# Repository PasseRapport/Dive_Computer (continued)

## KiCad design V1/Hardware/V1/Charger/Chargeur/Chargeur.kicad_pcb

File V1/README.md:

# Freediving Computer

A freediving computer prototype I built to test two main ideas: **tap navigation via accelerometer** and **wireless charging** in a completely sealed case.

As a maker, building waterproof buttons and moving parts that survive water pressure without leaking is nearly impossible. To avoid leaks, I skipped physical buttons and external connectors entirely:
1. **Tap navigation** — tapping the case scrolls and selects menus; the accelerometer detects the shock direction.
2. **Wireless charging** — sealed inside the case with an LTC4120 receiver, powered by a custom induction dock.
3. **Magnetic power switch** — an external magnet disconnects the battery so it doesn't drain when stored.
4. **Custom 4-layer PCB** — designed around the form factor of an off-the-shelf color OLED module.

> **Status**: This V1 worked and proved the concept. I am now working on a **V2** that is more compact, with better integration and additional features.

---

## Demo

<p align="center"><em>Tap-based navigation through the interface — accelerometer detects directional impacts on the casing.</em></p>

<p align="center"><em>Live depth tracking during a test — automatic dive detection and surface recovery timer.</em></p>

---

## Key Features

| Category | Details |
|---|---|
| **Depth & Temperature** | Real-time tracking via MS5837-30BA (±2 mm resolution, 300–1200 hPa). Automatic fresh/salt water density compensation. |
| **Dive State Machine** | Auto-triggers at 1.0 m depth. Tracks dive time, max depth per dive, and session statistics. |
| **Surface Recovery Timer** | Starts automatically on surfacing. Color-coded: red until 2× dive time, then green. Auto-hides after 10 min. |
| **Session Statistics** | Max dive time, max depth, total dives, and device run time — all tracked per session. |
| **Tap Navigation** | LIS2DUX12 accelerometer detects directional taps on the casing. Left/right to scroll, down to select. No buttons, no dynamic seals. |
| **Magnetic Battery Cutoff** | Integrated magnetic switch isolates the LiPo battery with an external magnet (true 0 µA shelf storage while sealed). |
| **Wireless Charging** | Completely sealed enclosure — power delivered through the case via LTC4120 wireless power receiver. |
| **Display** | 1.27" SSD1351 color OLED (128×96), driven over SPI with DMA. LVGL handles 60 fps animated transitions. |
| **Battery Monitoring** | ADC with hardware calibration curve. Voltage divider maps LiPo range (3.0–4.2 V) to percentage. |
| **Deep Sleep** | Full power-off via menu. GPIO wakeup from accelerometer interrupt. OLED and SPI bus shut down cleanly. |

---

## Mechanical Design

The housing is a two-part sandwich assembly designed without push-buttons, external connectors, or dynamic seals. Waterproofing relies entirely on static seals: a perimeter O-ring evenly compressed between the two halves by 12 M2 screws, and a front protective glass bonded with UV-cure resin. The only physical control is an external magnetic slider that switches power through the solid case wall without any hull penetration.

<p align="center">
  <a href="https://cad.onshape.com/documents/cc2f090fad22f578b68190d0/w/ffbf50c58a8e366da5acdcdc/e/88baec5796e801b1a2b4a1f3">
    View the 3D model on Onshape ↗
  </a>
</p>

---

## Hardware Architecture

The electronics are split between the wrist unit and a dedicated charging dock.

### 1. Dive Computer Board (Wrist Unit)

The core electronics are built around a custom **4-layer PCB** designed in KiCad, dimensioned to mate directly with an off-the-shelf color OLED module:

- **Form Factor & Display**: Sourced a compact 1.27" 128×96 color OLED module (SSD1351 controller, SPI) and tailored the custom 4-layer PCB and enclosure footprint around this geometry.
- **MCU**: ESP32-C3 (RISC-V core, low power modes, BLE).
- **Pressure Sensor**: TE MS5837-30BA (gel-protected submersible pressure & temperature sensor on I2C).
- **Accelerometer**: ST LIS2DUX12 (ultra-low-power, configured for shock/tap detection with hardware interrupt).
- **Wireless Power Receiver**: Analog Devices LTC4120 with an internal Würth planar receiver coil (WE-WPCC-RX), delivering CC/CV charging to the internal 3.7V LiPo cell.
- **Magnetic Power Switch**: Integrated Hall-effect sensor / magnetic switch controlling a P-MOSFET gate, enabling complete physical battery disconnection via an external magnet without unsealing the housing.

| Component | Part | Role |
|---|---|---|
| MCU | ESP32-C3 | RISC-V core, sensor aggregation, LVGL rendering |
| Pressure Sensor | MS5837-30BA | Absolute pressure & temperature (I2C @ 100 kHz) |
| Accelerometer | LIS2DUX12 | Tap detection with hardware interrupt (I2C) |
| Wireless Charger RX | LTC4120 | Wireless power receiver & CC/CV LiPo charger |
| Magnetic Disconnect | A1102 + P-MOS | Physical battery isolation via external magnet (0 µA storage) |
| Display Module | SSD1351 (Off-the-shelf) | 1.27" 128×96 color OLED (SPI with DMA) |
| Battery | LiPo 3.7V | Single cell, monitored via calibrated ADC voltage divider |

### 2. Wireless Charger Dock (Transmitter)

A companion transmitter base powered via USB-C:

| Component | Part | Role |
|---|---|---|
| Transmitter IC | LTC4125 | 5W AutoResonant wireless power transmitter |
| Transmit Coil | Würth WE-WPCC-TX | 24 µH primary coil for inductive power transfer |
| Input | USB-C (5V) | Power supply |

Source files (KiCad projects, gerbers, BOM): [`Hardware/V1/`](Hardware/V1/)

---

## Software Architecture

The firmware is written in **C** on **ESP-IDF** with **FreeRTOS**. The codebase follows an MVC pattern:

```
Software/DiveComputer/main/
├── main.c                  # App entry, event loop, screen state machine
├── components/
│   ├── pressure_sensor.c   # MS5837 driver, depth calculation, calibration
│   ├── accelerometer.c     # LIS2DUX12 tap detection (ISR + burst analysis)
│   ├── battery.c           # ADC with hardware calibration curve
│   └── oled_display.c      # SSD1351 init, SPI+DMA, LVGL driver
└── ui/
    ├── ui_model.h          # Global state structure (dive_state_t)
    ├── ui_controller.c     # Dive logic, timers, brightness control
    ├── ui_layout.c         # All LVGL screens and refresh functions
    └── ui_layout.h         # Public UI API
```

### Task Model

| Task | Core | Priority | Rate | Role |
|---|---|---|---|---|
| `dive_sensor_task` | 1 | 5 | 4 Hz | Reads pressure sensor, computes depth, updates model |
| `lvgl_port_task` | 0 | 5 | 100 Hz | LVGL rendering and screen refresh |
| `tap_analyzer_task` | 0 | 10 | Event-driven | Wakes on accelerometer interrupt, analyzes shock direction |
| Main loop | 0 | 1 | 50 Hz | Polls tap events, drives screen state machine |

### Dive State Machine

```
                 depth > 1.0m
   ┌──────────┐ ───────────────> ┌──────────┐
   │ SURFACE  │                  │  DIVING  │ <──────┐
   └──────────┘                  └──────────┘        │
        ^                             │              │ depth > 1.0m
        │                             │ depth < 0.3m │ (next dive)
        │                             v              │
        │                      ┌─────────────┐       │
        └───────────────────── │  POST-DIVE  │ ──────┘
           recovery >= 10 min  │ (Recovery)  │
                               └─────────────┘

```

### Tap Detection Pipeline

The accelerometer's hardware tap interrupt wakes the ESP32, which performs a 100-sample burst read (~10 ms) to capture the full shock waveform. The axis with the largest amplitude delta wins, and its sign determines the direction. A 2000-unit noise floor filter rejects accidental vibrations.

```
[HW Interrupt] ──> [ISR Queue] ──> [Burst Read (100 samples)] ──> [Axis Analysis] ──> [Direction Filter] ──> [UI Event]
```

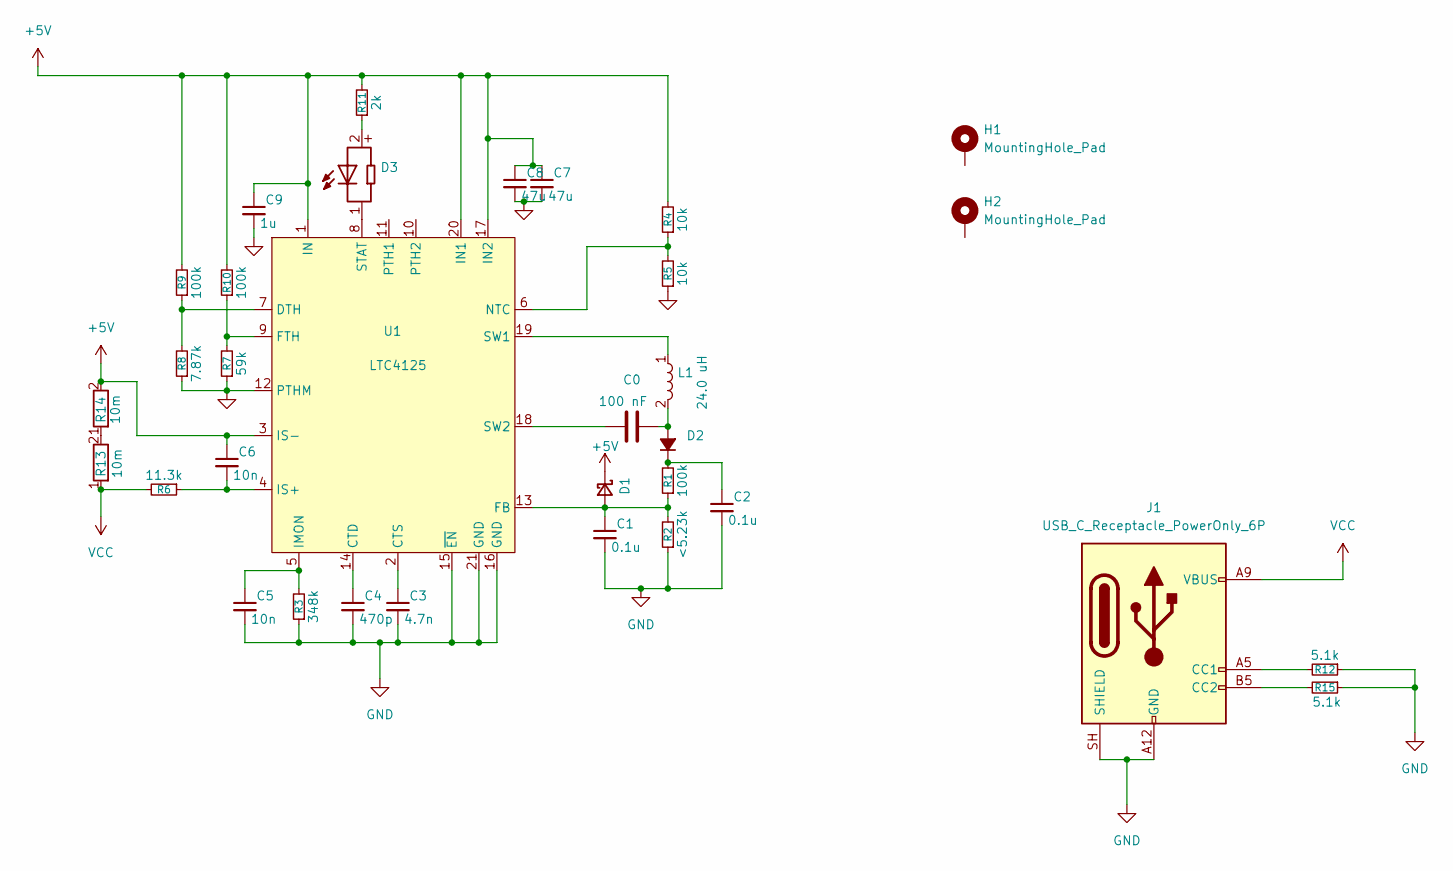
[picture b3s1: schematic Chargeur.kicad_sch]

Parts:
C0: 100 nF; C_Wurth_WCAP-FTBP-P7.5L10.5W5H11; Voltage 160; Part Number 890443322001CS
C1, C2: 0.1u; C_0603_1608Metric
C3: 4.7n; C_0603_1608Metric
C4: 470p; C_0603_1608Metric
C5, C6: 10n; C_0603_1608Metric
C7, C8: 47u; C_1206_3216Metric
C9: 1u; C_1206_3216Metric
D1: D_Schottky_Small; D_MicroSMP_LargeCathode
D2: D_Small_Filled; D_SOD-523
D3: 3535_150353BS74500; D_Wurth_WL-SMDC-3535; Part Number 150353BS74500
H1, H2: MountingHole_Pad; MountingHole_3.2mm_M3_DIN965_Pad
J1: USB_C_Receptacle_PowerOnly_6P; USB_C_Receptacle_GCT_USB4125-xx-x-0190_6P_TopMnt_Horizontal
L1: 24.0 uH; L_Wurth_WE-WPCC-TX_760308101107; Part Number 760308101107
R1, R9, R10: 100k; R_0603_1608Metric
R2: <5.23k; R_0603_1608Metric
R3: 348k; R_0603_1608Metric
R4, R5: 10k; R_0603_1608Metric
R6: 11.3k; R_0603_1608Metric
R7: 59k; R_0603_1608Metric
R8: 7.87k; R_0603_1608Metric
R11: 2k; R_0603_1608Metric
R12, R15: 5.1k; R_0603_1608Metric
R13, R14: 10 mohm; R_Wurth_WRIS-PSMB-1206_L3.2W1.6H0.28; Part Number 580060732021
U1: LTC4125; QFN-20-1EP_4x5mm_P0.5mm_EP2.65x3.65mm

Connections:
+5V: C6.1, C7.1, C8.1, C9.1, D1.1 (K), R4.2, R9.2, R10.2, R11.2, R14.2, U1.1 (IN), U1.3 (IS-), U1.17 (IN2), U1.20 (IN1)
GND: C1.2, C2.2, C3.2, C4.2, C5.2, C7.2, C8.2, C9.2, J1.A12 (GND), J1.B12 (GND), J1.SH (SHIELD), R2.1, R3.1, R5.1, R7.1, R8.1, R12.1, R15.1, U1.12 (PTHM), U1.15 (~EN), U1.16 (GND), U1.21 (GND)
unnamed: C1.1, D1.2 (A), R1.1, R2.2, U1.13 (FB)
unnamed: C0.2, D2.2 (A), L1.2
unnamed: C2.1, D2.1 (K), R1.2
unnamed: D3.2 (+), R11.1
unnamed: D3.1 (-), U1.8 (STAT)
unnamed: J1.A5 (CC1), R12.2
unnamed: J1.B5 (CC2), R15.2
unnamed: R13.2, R14.1
unnamed: C4.1, U1.14 (CTD)
unnamed: C3.1, U1.2 (CTS)
unnamed: R8.2, R9.1, U1.7 (DTH)
unnamed: R7.2, R10.1, U1.9 (FTH)
unnamed: C5.1, R3.2, U1.5 (IMON)
unnamed: C6.2, R6.1, U1.4 (IS+)
unnamed: R4.1, R5.2, U1.6 (NTC)
unnamed: L1.1, U1.19 (SW1)
unnamed: C0.1, U1.18 (SW2)
VCC: J1.A9 (VBUS), J1.B9 (VBUS), R6.2, R13.1

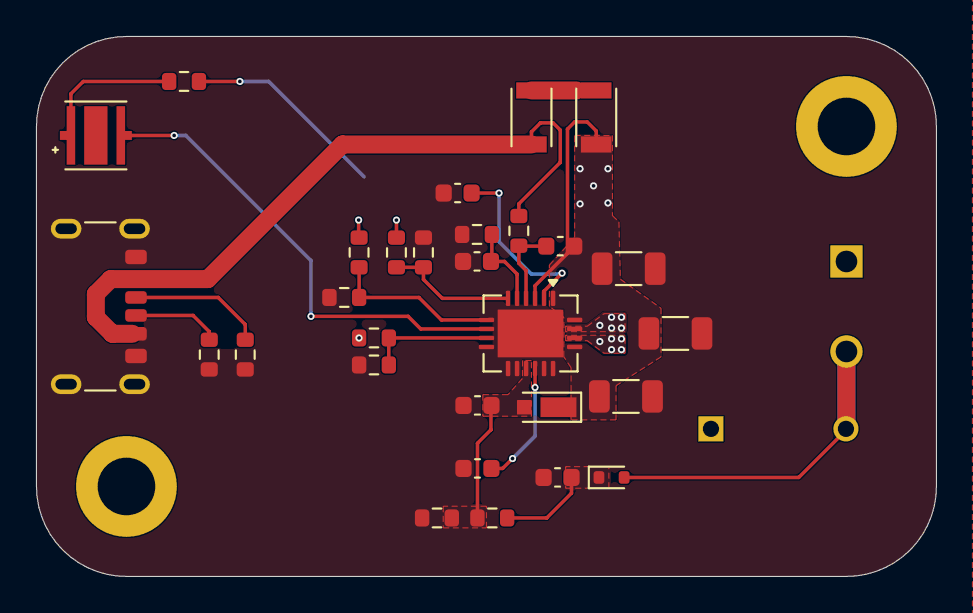
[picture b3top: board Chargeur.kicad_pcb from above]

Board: 2 copper layers, 50.0 x 30.0 mm, 33 parts (0 on the bottom side), 20 nets.

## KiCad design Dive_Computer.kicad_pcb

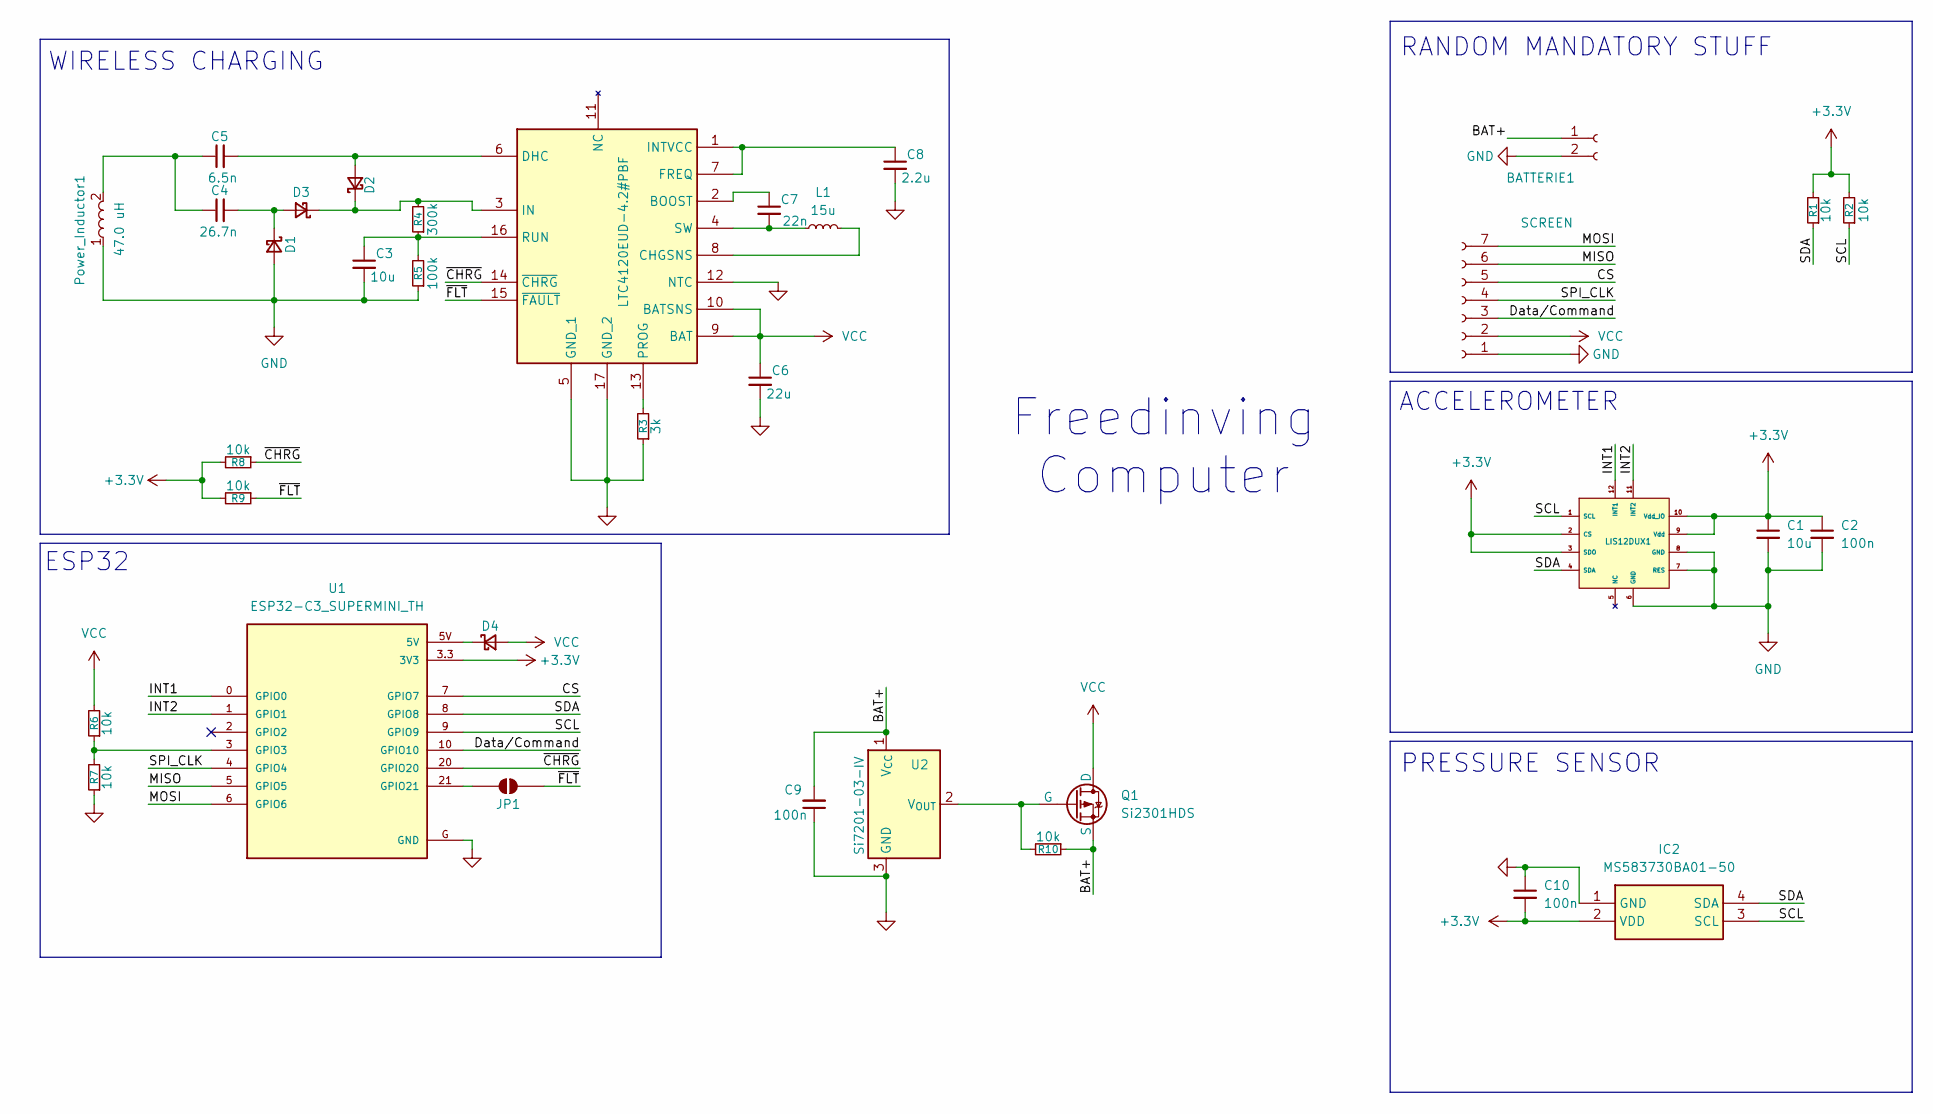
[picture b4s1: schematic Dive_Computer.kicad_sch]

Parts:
BATTERIE1: BAT; Hirose_DF13-02P-1.25DSA_1x02_P1.25mm_Vertical
C1: 10u; C_0603_1608Metric
C2, C9, C10: 100n; C_0603_1608Metric
C3: 10u; C_1210_3225Metric
C4: 26.7n; C_0603_1608Metric
C5: 6.5n; C_0603_1608Metric
C6: 22u; C_0603_1608Metric
C7: 22n; C_0603_1608Metric
C8: 2.2u; C_0603_1608Metric
D1, D2, D3, D4: MSS2P2-M3/89A; D_MicroSMP_LargeCathode
IC1: LTC4120EUD-4.2#PBF; QFN-16-1EP_3x3mm_P0.5mm_EP1.7x1.7mm; Manufacturer_Part_Number LTC4120EUD-4.2#PBF; Mouser Part Number 584-C4120EUD-4.2PBF
IC2: MS583730BA01-50; TE_MS5837-xxBA; Manufacturer_Part_Number MS583730BA01-50; Mouser Part Number 824-MS583730BA01-50
J1: SCREEN; Hirose_DF13-07P-1.25DSA_1x07_P1.25mm_Vertical
JP1: SolderJumper_2_Open; SolderJumper-2_P1.3mm_Open_RoundedPad1.0x1.5mm
L1: 15u; L_APV_ANR4018
LIS12DUX1: LGA-12_2x2mm_P0.5mm
Power_Inductor1: 47.0 uH; PinHeader_1x02_P2.54mm_Vertical; Part Number 760308101303
Q1: Si2301HDS; TSOT-23
R1, R2, R6, R7, R8, R9, R10: 10k; R_0603_1608Metric
R3: 3k; R_0603_1608Metric
R4: 300k; R_0603_1608Metric
R5: 100k; R_0603_1608Metric
U1: ESP32-C3_SUPERMINI_TH; MODULE_ESP32-C3_SUPERMINI_TH
U2: Si7201-03-IV; SOT-23

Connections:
+3.3V: C1.1, C2.1, C10.2, IC2.2 (VDD), LIS12DUX1.2 (CS), LIS12DUX1.3 (SDO), LIS12DUX1.9 (Vdd), LIS12DUX1.10 (Vdd_IO), R1.2, R2.2, R8.2, R9.2, U1.3.3 (3V3)
/BAT+: BATTERIE1.1, C9.2, Q1.3 (S), R10.1, U2.1 (V_{CC})
/CS: J1.5, U1.7 (GPIO7)
/Data/Command: J1.3, U1.10 (GPIO10)
/INT1: LIS12DUX1.12 (INT1), U1.0 (GPIO0)
/INT2: LIS12DUX1.11 (INT2), U1.1 (GPIO1)
/MISO: J1.6, U1.5 (GPIO5)
/MOSI: J1.7, U1.6 (GPIO6)
/SCL: IC2.3 (SCL), LIS12DUX1.1 (SCL), R2.1, U1.9 (GPIO9)
/SDA: IC2.4 (SDA), LIS12DUX1.4 (SDA), R1.1, U1.8 (GPIO8)
/SPI_CLK: J1.4, U1.4 (GPIO4)
/~CHRG: IC1.14 (~CHRG), R8.1, U1.20 (GPIO20)
/~FLT: IC1.15 (~FAULT), JP1.2 (B), R9.1
GND: BATTERIE1.2, C1.2, C2.2, C3.2, C6.2, C8.2, C9.1, C10.1, D1.2 (A), IC1.5 (GND_1), IC1.12 (NTC), IC1.17 (GND_2), IC2.1 (GND), J1.1, LIS12DUX1.6 (GND), LIS12DUX1.7 (RES), LIS12DUX1.8 (GND), Power_Inductor1.1, R3.1, R5.1, R7.1, U1.G (GND), U2.3 (GND)
unnamed: C4.1, C5.1, Power_Inductor1.2
unnamed: C4.2, D1.1 (K), D3.2 (A)
unnamed: C5.2, D2.2 (A), IC1.6 (DHC)
unnamed: D2.1 (K), D3.1 (K), IC1.3 (IN), R4.2
unnamed: D4.1 (K), U1.5V
unnamed: C7.1, IC1.2 (BOOST)
unnamed: IC1.8 (CHGSNS), L1.2
unnamed: C8.1, IC1.1 (INTVCC), IC1.7 (FREQ)
unnamed: IC1.13 (PROG), R3.2
unnamed: C3.1, IC1.16 (RUN), R4.1, R5.2
unnamed: C7.2, IC1.4 (SW), L1.1
unnamed: JP1.1 (A), U1.21 (GPIO21)
unnamed: Q1.2 (G), R10.2, U2.2 (V_{OUT})
unnamed: R6.1, R7.2, U1.3 (GPIO3)
VCC: C6.1, D4.2 (A), IC1.9 (BAT), IC1.10 (BATSNS), J1.2, Q1.1 (D), R6.2

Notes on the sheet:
PRESSURE SENSOR
ACCELEROMETER
RANDOM MANDATORY STUFF
Freedinving Computer
ESP32
WIRELESS CHARGING

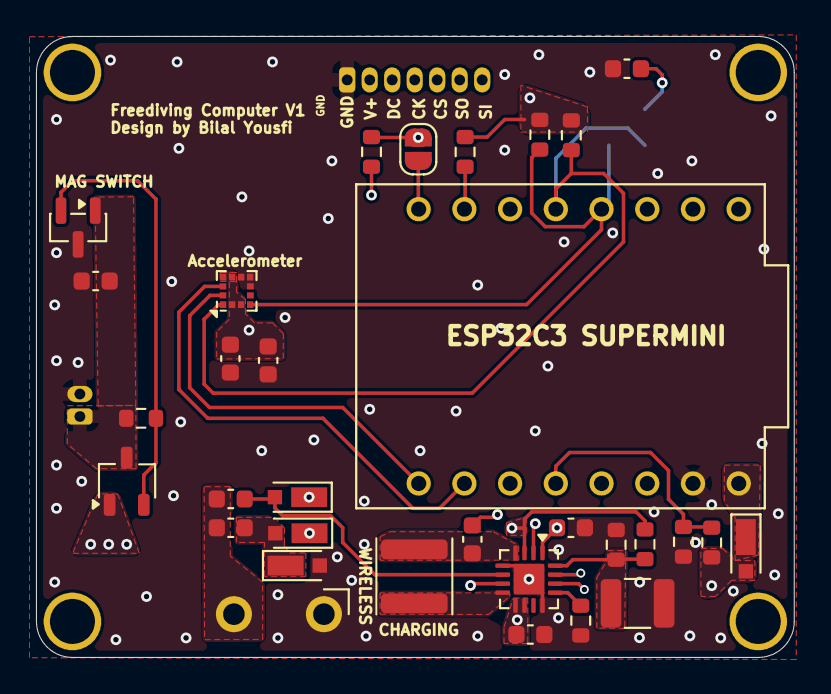
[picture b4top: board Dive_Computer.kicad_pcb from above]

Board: 4 copper layers, 42.1 x 34.5 mm, 35 parts (1 on the bottom side), 29 nets.

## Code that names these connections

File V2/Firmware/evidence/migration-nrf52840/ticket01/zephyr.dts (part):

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			status = "okay";                    /* in zephyr/dts/arm/nordic/nrf52840.dtsi:61 */
			#address-cells = < 0x1 >;           /* in zephyr/dts/arm/nordic/nrf52840.dtsi:62 */
			#size-cells = < 0x1 >;              /* in zephyr/dts/arm/nordic/nrf52840.dtsi:63 */
			gpio-as-nreset;                     /* in ../../../../tmp/dive-nrf52840-ticket01/V2/Firmware/boards/nordic/dc_v2_2/dc_v2_2_nrf52840.dts:57 */
			nfct-pins-as-gpios;                 /* in ../../../../tmp/dive-nrf52840-ticket01/V2/Firmware/boards/nordic/dc_v2_2/dc_v2_2_nrf52840.dts:58 */
		};

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			acc: lis2dux12@19 {
				compatible = "st,lis2dux12";     /* in ../../../../tmp/dive-nrf52840-ticket01/V2/Firmware/boards/nordic/dc_v2_2/dc_v2_2_nrf52840.dts:88 */
				reg = < 0x19 >;                  /* in ../../../../tmp/dive-nrf52840-ticket01/V2/Firmware/boards/nordic/dc_v2_2/dc_v2_2_nrf52840.dts:89 */
				int1-gpios = < &gpio0 0x2 0x0 >; /* in ../../../../tmp/dive-nrf52840-ticket01/V2/Firmware/app.overlay:87 */
				status = "okay";                 /* in ../../../../tmp/dive-nrf52840-ticket01/V2/Firmware/app.overlay:88 */
			};

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			enc: tmag3001@35 {
				compatible = "ti,tmag3001";     /* in ../../../../tmp/dive-nrf52840-ticket01/V2/Firmware/boards/nordic/dc_v2_2/dc_v2_2_nrf52840.dts:100 */
				reg = < 0x35 >;                 /* in ../../../../tmp/dive-nrf52840-ticket01/V2/Firmware/boards/nordic/dc_v2_2/dc_v2_2_nrf52840.dts:101 */
				int-gpios = < &gpio0 0x3 0x1 >; /* in ../../../../tmp/dive-nrf52840-ticket01/V2/Firmware/app.overlay:92 */
			};

			/* node '/soc/i2c@40003000/veml6035@10' defined in ../../../../tmp/dive-nrf52840-ticket01/V2/Firmware/boards/nordic/dc_v2_2/dc_v2_2_nrf52840.dts:105 */
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			pinctrl-1 = < &spi1_sleep >;    /* in ../../../../tmp/dive-nrf52840-ticket01/V2/Firmware/boards/nordic/dc_v2_2/dc_v2_2_nrf52840.dts:120 */
			pinctrl-names = "default",
			                "sleep";        /* in ../../../../tmp/dive-nrf52840-ticket01/V2/Firmware/boards/nordic/dc_v2_2/dc_v2_2_nrf52840.dts:121 */
			cs-gpios = < &gpio0 0xb 0x1 >;  /* in ../../../../tmp/dive-nrf52840-ticket01/V2/Firmware/app.overlay:76 */

			/* node '/soc/spi@40004000/lpm013m091a@0' defined in ../../../../tmp/dive-nrf52840-ticket01/V2/Firmware/boards/nordic/dc_v2_2/dc_v2_2_nrf52840.dts:127 */
			lcd: lpm013m091a@0 {
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				spi-max-frequency = < 0x7a1200 >; /* in ../../../../tmp/dive-nrf52840-ticket01/V2/Firmware/boards/nordic/dc_v2_2/dc_v2_2_nrf52840.dts:130 */
				width = < 0x140 >;                /* in ../../../../tmp/dive-nrf52840-ticket01/V2/Firmware/boards/nordic/dc_v2_2/dc_v2_2_nrf52840.dts:131 */
				height = < 0x12c >;               /* in ../../../../tmp/dive-nrf52840-ticket01/V2/Firmware/boards/nordic/dc_v2_2/dc_v2_2_nrf52840.dts:132 */
				reset-gpios = < &gpio1 0x9 0x1 >; /* in ../../../../tmp/dive-nrf52840-ticket01/V2/Firmware/app.overlay:81 */
				te-gpios = < &gpio0 0x1f 0x0 >;   /* in ../../../../tmp/dive-nrf52840-ticket01/V2/Firmware/app.overlay:82 */
			};
		};

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		};

		/* node '/soc/gpio@50000000' defined in zephyr/dts/arm/nordic/nrf52840.dtsi:565 */
		gpio0: gpio@50000000 {
			compatible = "nordic,nrf-gpio";              /* in zephyr/dts/arm/nordic/nrf52840.dtsi:566 */
			gpio-controller;                             /* in zephyr/dts/arm/nordic/nrf52840.dtsi:567 */
			reg = < 0x50000000 0x200 0x50000500 0x300 >; /* in zephyr/dts/arm/nordic/nrf52840.dtsi:568 */
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		};

		/* node '/soc/gpio@50000300' defined in zephyr/dts/arm/nordic/nrf52840.dtsi:576 */
		gpio1: gpio@50000300 {
			compatible = "nordic,nrf-gpio";              /* in zephyr/dts/arm/nordic/nrf52840.dtsi:577 */
			gpio-controller;                             /* in zephyr/dts/arm/nordic/nrf52840.dtsi:578 */
			reg = < 0x50000300 0x200 0x50000800 0x300 >; /* in zephyr/dts/arm/nordic/nrf52840.dtsi:579 */
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	zephyr,user {
		mcu-regout0-microvolt = < 0x1b7740 >; /* in ../../../../tmp/dive-nrf52840-ticket01/V2/Firmware/boards/nordic/dc_v2_2/dc_v2_2_nrf52840.dts:30 */
		mcu-regout0-uicr-vout = < 0x0 >;      /* in ../../../../tmp/dive-nrf52840-ticket01/V2/Firmware/boards/nordic/dc_v2_2/dc_v2_2_nrf52840.dts:31 */
		chg_n-gpios = < &gpio0 0xa 0x3 >;     /* in ../../../../tmp/dive-nrf52840-ticket01/V2/Firmware/app.overlay:71 */
	};

	/* node '/gpio-leds' defined in ../../../../tmp/dive-nrf52840-ticket01/V2/Firmware/app.overlay:29 */
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
		/* node '/gpio-leds/rail_1v2_1v8_en' defined in ../../../../tmp/dive-nrf52840-ticket01/V2/Firmware/app.overlay:32 */
		rail_1v2_1v8_en {
			gpios = < &gpio0 0x1c 0x0 >; /* in ../../../../tmp/dive-nrf52840-ticket01/V2/Firmware/app.overlay:33 */
		};

		/* node '/gpio-leds/rail_3v1_en' defined in ../../../../tmp/dive-nrf52840-ticket01/V2/Firmware/app.overlay:36 */
		rail_3v1_en {
			gpios = < &gpio0 0x1d 0x0 >; /* in ../../../../tmp/dive-nrf52840-ticket01/V2/Firmware/app.overlay:37 */
		};

		/* node '/gpio-leds/qi_en' defined in ../../../../tmp/dive-nrf52840-ticket01/V2/Firmware/app.overlay:40 */
		qi_en {
			gpios = < &gpio0 0x9 0x0 >; /* in ../../../../tmp/dive-nrf52840-ticket01/V2/Firmware/app.overlay:41 */
		};

		/* node '/gpio-leds/bl_pwm_mcu' defined in ../../../../tmp/dive-nrf52840-ticket01/V2/Firmware/app.overlay:44 */
		bl_pwm_mcu {
			gpios = < &gpio0 0x14 0x0 >; /* in ../../../../tmp/dive-nrf52840-ticket01/V2/Firmware/app.overlay:45 */
		};
	};

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	gpio-keys {
		compatible = "zephyr,gpio-keys"; /* in ../../../../tmp/dive-nrf52840-ticket01/V2/Firmware/app.overlay:55 */

		/* node '/gpio-keys/int_acc1' defined in ../../../../tmp/dive-nrf52840-ticket01/V2/Firmware/app.overlay:57 */
		int_acc1 {
			gpios = < &gpio0 0x2 0x0 >; /* in ../../../../tmp/dive-nrf52840-ticket01/V2/Firmware/app.overlay:58 */
		};

		/* node '/gpio-keys/int_enc' defined in ../../../../tmp/dive-nrf52840-ticket01/V2/Firmware/app.overlay:61 */
		int_enc {
			gpios = < &gpio0 0x3 0x1 >; /* in ../../../../tmp/dive-nrf52840-ticket01/V2/Firmware/app.overlay:62 */
		};

		/* node '/gpio-keys/int_light' defined in ../../../../tmp/dive-nrf52840-ticket01/V2/Firmware/app.overlay:65 */
		int_light {
			gpios = < &gpio0 0x1e 0x1 >; /* in ../../../../tmp/dive-nrf52840-ticket01/V2/Firmware/app.overlay:66 */
		};
	};
};
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
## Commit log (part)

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2026-04-27 Start
2026-04-27 Shematic
2026-04-28 Schematic finished
2026-04-29 Schematic update
2026-04-30 Routage terminé
2026-04-30 Added 3D models
2026-05-15 UI
    The UI is mostly done
    The core architecture is up and running
2026-05-15 added the software
2026-05-17 Readme update
2026-05-18 Revise README.md for improved presentation and details
    Updated README to enhance formatting and clarity, including new sections and features.
2026-05-18 Revise README.md for software architecture and UI
    Updated README.md to enhance software architecture and UI details, including FreeRTOS task management and tap-to-control navigation.
2026-06-08 Chargeur
2026-06-12 jaaj
